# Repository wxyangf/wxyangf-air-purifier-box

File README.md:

Corsi-Rosenthol Inspired Air Purifier

Onshape Available Here: https://cad.onshape.com/documents/9fe4c8aaf9f949d23d7b46f2/w/0d3218e59a3f068a2d390f4a/e/8d3bb73142d813d5a04eb98a (This Is Based on the version tagged "Public Release")

The concept was to have a Corsi-Rosenthol like design, but a bit more refined.

The big problem that I aimed to address with this design is the difficulty of changing the filters in a regular Corsi-Rosenthol air purifier.

no flow rate tests, because it will heavily depend on the fans you decide to use.

TODO:

* write a proper bom
* add assembly instructions
* update the clip design to not self loosen if turned CCW
* add design for decorative side panels

images:

Notes:

I was too lazy to design my own so voltage regulator part used: https://www.amazon.com/dp/B07VVXF7YX

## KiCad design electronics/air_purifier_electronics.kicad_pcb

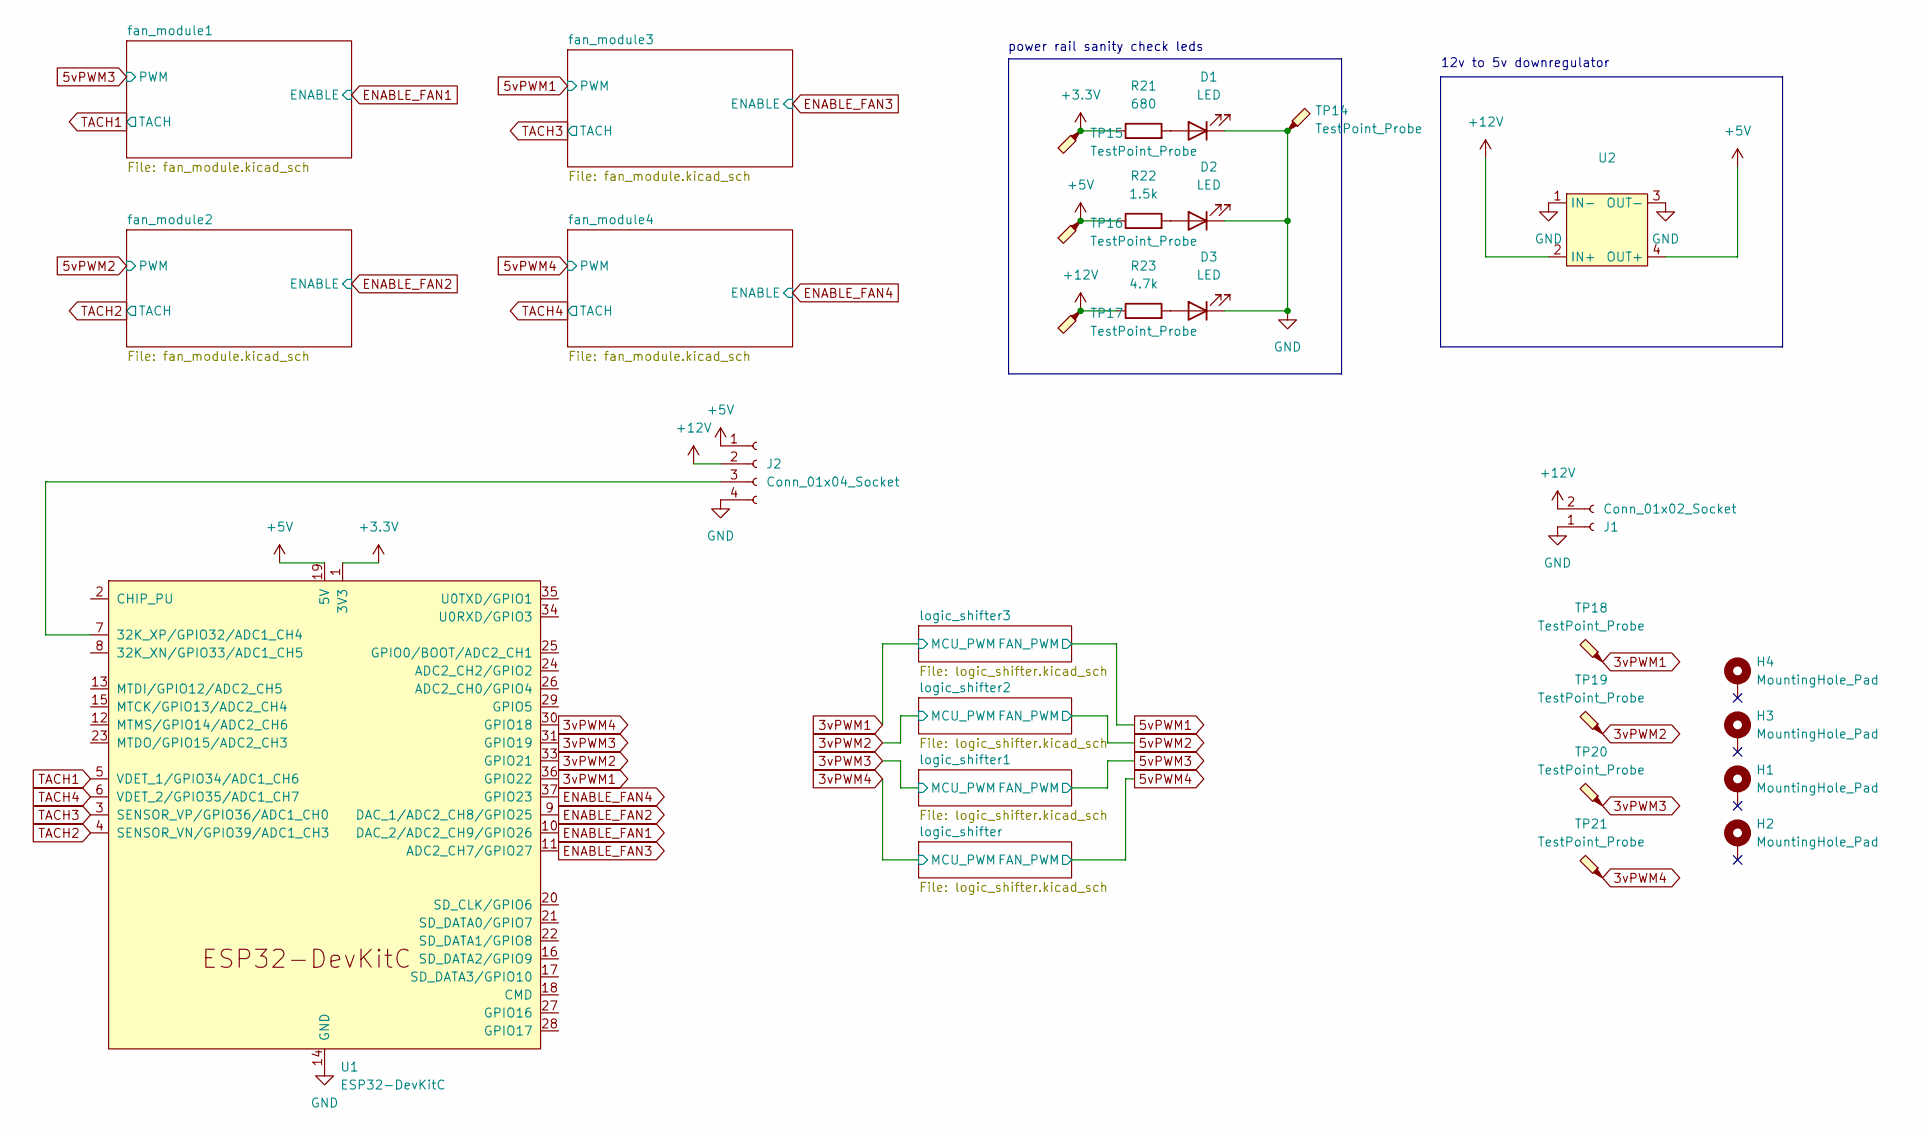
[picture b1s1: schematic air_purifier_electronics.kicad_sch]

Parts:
D1, D2, D3: LED; LED_0805_2012Metric_Pad1.15x1.40mm_HandSolder; LCSC C2296
H1, H2, H3, H4: MountingHole_Pad; MountingHole_3.2mm_M3_DIN965_Pad
J1: Conn_01x02_Socket; AMASS_XT30U-M_1x02_P5.0mm_Vertical
J2: Conn_01x04_Socket; TerminalBlock_Altech_AK300-4_P5.00mm
R21: 680; R_0805_2012Metric_Pad1.20x1.40mm_HandSolder; LCSC C17798
R22: 1.5k; R_0805_2012Metric_Pad1.20x1.40mm_HandSolder; LCSC C4310
R23: 4.7k; R_0805_2012Metric_Pad1.20x1.40mm_HandSolder; LCSC C22356680
TP14, TP15, TP16, TP17, TP18, TP19, TP20, TP21: TestPoint_Probe; TestPoint_THTPad_2.0x2.0mm_Drill1.0mm
U1: ESP32-DevKitC; nodemcu-32s
U2: buck_boost_module

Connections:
3vPWM1: TP18.1, U1.36 (GPIO22); also elsewhere on the board
3vPWM2: TP19.1, U1.33 (GPIO21); also elsewhere on the board
3vPWM3: TP20.1, U1.31 (GPIO19); also elsewhere on the board
3vPWM4: TP21.1, U1.30 (GPIO18); also elsewhere on the board
+3.3V: R21.1, TP15.1, U1.1 (3V3); also elsewhere on the board
+5V: J2.1, R22.1, TP16.1, U1.19 (5V), U2.4 (OUT+)
+12V: J1.2, J2.2, R23.1, TP17.1, U2.2 (IN+); also elsewhere on the board
ENABLE_FAN1: U1.10 (DAC_2/ADC2_CH9/GPIO26); also elsewhere on the board
ENABLE_FAN2: U1.9 (DAC_1/ADC2_CH8/GPIO25); also elsewhere on the board
ENABLE_FAN3: U1.11 (ADC2_CH7/GPIO27); also elsewhere on the board
ENABLE_FAN4: U1.37 (GPIO23); also elsewhere on the board
GND: D1.1 (K), D2.1 (K), D3.1 (K), J1.1, J2.4, TP14.1, U1.14 (GND), U1.32 (GND), U1.38 (GND), U2.1 (IN-), U2.3 (OUT-); also elsewhere on the board
unnamed: D1.2 (A), R21.2
unnamed: D2.2 (A), R22.2
unnamed: D3.2 (A), R23.2
unnamed: J2.3, U1.7 (32K_XP/GPIO32/ADC1_CH4)
TACH1: U1.5 (VDET_1/GPIO34/ADC1_CH6); also elsewhere on the board
TACH2: U1.4 (SENSOR_VN/GPIO39/ADC1_CH3); also elsewhere on the board
TACH3: U1.3 (SENSOR_VP/GPIO36/ADC1_CH0); also elsewhere on the board
TACH4: U1.6 (VDET_2/GPIO35/ADC1_CH7); also elsewhere on the board

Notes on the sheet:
12v to 5v downregulator
power rail sanity check leds

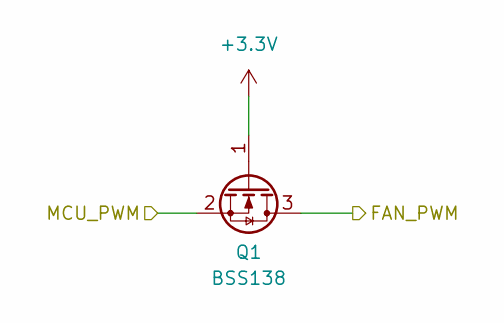
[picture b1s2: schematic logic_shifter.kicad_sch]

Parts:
Q1: BSS138; SOT-23

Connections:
3vPWM4: Q1.2 (S); also elsewhere on the board
5vPWM4: Q1.3 (D); also elsewhere on the board
+3.3V: Q1.1 (G); also elsewhere on the board

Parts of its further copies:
Q2, Q3, Q4: BSS138; SOT-23

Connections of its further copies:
3vPWM1: Q2.2 (S); also elsewhere on the board
3vPWM2: Q3.2 (S); also elsewhere on the board
3vPWM3: Q4.2 (S); also elsewhere on the board
5vPWM1: Q2.3 (D); also elsewhere on the board
5vPWM2: Q3.3 (D); also elsewhere on the board
5vPWM3: Q4.3 (D); also elsewhere on the board
+3.3V: Q2.1 (G), Q3.1 (G), Q4.1 (G); also elsewhere on the board

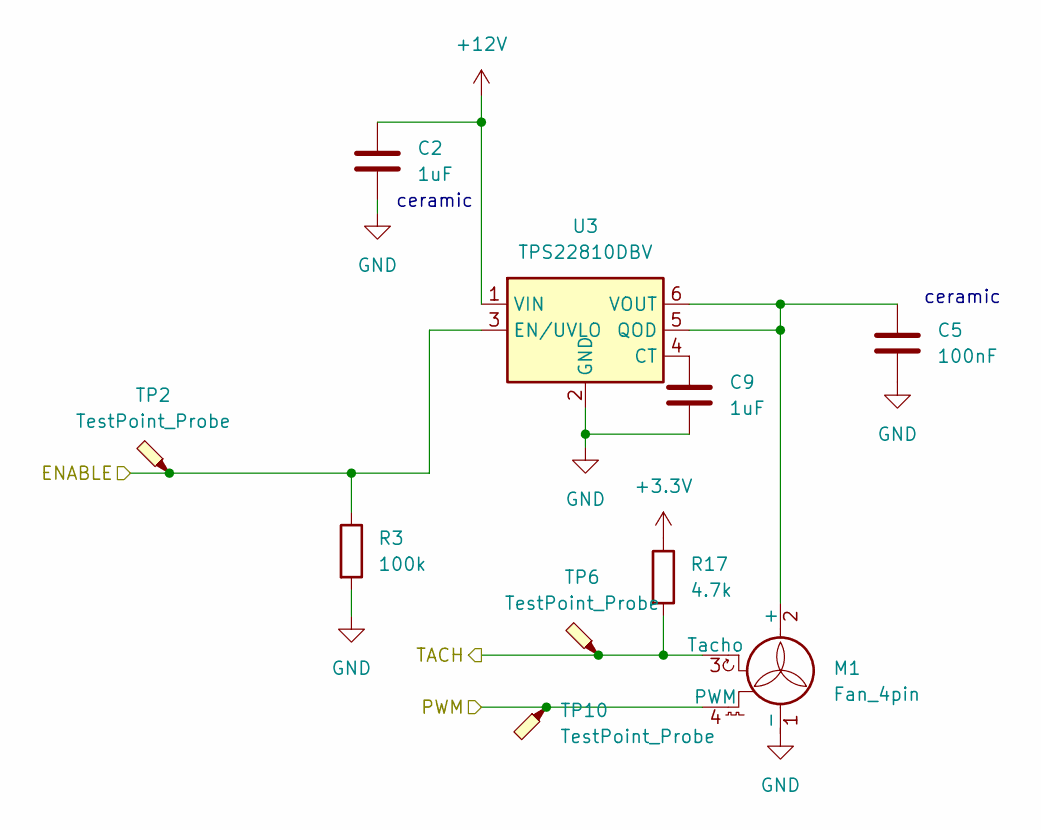
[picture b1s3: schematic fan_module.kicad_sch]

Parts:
C2, C9: 1uF; C_0805_2012Metric_Pad1.18x1.45mm_HandSolder
C5: 100nF; C_0805_2012Metric_Pad1.18x1.45mm_HandSolder
M1: Fan_4pin; FanPinHeader_1x04_P2.54mm_Vertical; LCSC C19795120
R3: 100k; R_0805_2012Metric_Pad1.20x1.40mm_HandSolder; LCSC C22356675
R17: 4.7k; R_0805_2012Metric_Pad1.20x1.40mm_HandSolder; LCSC C22356680
TP2, TP6, TP10: TestPoint_Probe; TestPoint_THTPad_2.0x2.0mm_Drill1.0mm
U3: TPS22810DBV; SOT-23-6

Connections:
5vPWM4: M1.4 (PWM), TP10.1; also elsewhere on the board
+3.3V: R17.1; also elsewhere on the board
+12V: C2.1, U3.1 (VIN); also elsewhere on the board
ENABLE_FAN4: R3.1, TP2.1, U3.3 (EN/UVLO); also elsewhere on the board
GND: C2.2, C5.2, C9.2, M1.1 (-), R3.2, U3.2 (GND); also elsewhere on the board
unnamed: C5.1, M1.2 (+), U3.5 (QOD), U3.6 (VOUT)
unnamed: C9.1, U3.4 (CT)
TACH4: M1.3 (Tacho), R17.2, TP6.1; also elsewhere on the board

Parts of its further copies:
C1, C3, C4, C10, C11, C12: 1uF; C_0805_2012Metric_Pad1.18x1.45mm_HandSolder
C6, C7, C8: 100nF; C_0805_2012Metric_Pad1.18x1.45mm_HandSolder
M2, M3, M4: Fan_4pin; FanPinHeader_1x04_P2.54mm_Vertical; LCSC C19795120
R6, R10, R14: 100k; R_0805_2012Metric_Pad1.20x1.40mm_HandSolder; LCSC C22356675
R18, R19, R20: 4.7k; R_0805_2012Metric_Pad1.20x1.40mm_HandSolder; LCSC C22356680
TP3, TP4, TP5, TP7, TP8, TP9, TP11, TP12, TP13: TestPoint_Probe; TestPoint_THTPad_2.0x2.0mm_Drill1.0mm
U4, U5, U6: TPS22810DBV; SOT-23-6

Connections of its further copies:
5vPWM1: M4.4 (PWM), TP13.1; also elsewhere on the board
5vPWM2: M3.4 (PWM), TP12.1; also elsewhere on the board
5vPWM3: M2.4 (PWM), TP11.1; also elsewhere on the board
+3.3V: R18.1, R19.1, R20.1; also elsewhere on the board
+12V: C1.1, C3.1, C4.1, U4.1 (VIN), U5.1 (VIN), U6.1 (VIN); also elsewhere on the board
ENABLE_FAN1: R6.1, TP3.1, U4.3 (EN/UVLO); also elsewhere on the board
ENABLE_FAN2: R10.1, TP4.1, U5.3 (EN/UVLO); also elsewhere on the board
ENABLE_FAN3: R14.1, TP5.1, U6.3 (EN/UVLO); also elsewhere on the board
GND: C1.2, C3.2, C4.2, C6.2, C7.2, C8.2, C10.2, C11.2, C12.2, M2.1 (-), M3.1 (-), M4.1 (-), R6.2, R10.2, R14.2, U4.2 (GND), U5.2 (GND), U6.2 (GND); also elsewhere on the board
unnamed: C6.1, M2.2 (+), U4.5 (QOD), U4.6 (VOUT)
unnamed: C7.1, M3.2 (+), U5.5 (QOD), U5.6 (VOUT)
unnamed: C8.1, M4.2 (+), U6.5 (QOD), U6.6 (VOUT)
unnamed: C10.1, U4.4 (CT)
unnamed: C11.1, U5.4 (CT)
unnamed: C12.1, U6.4 (CT)
TACH1: M2.3 (Tacho), R18.2, TP7.1; also elsewhere on the board
TACH2: M3.3 (Tacho), R19.2, TP8.1; also elsewhere on the board
TACH3: M4.3 (Tacho), R20.2, TP9.1; also elsewhere on the board

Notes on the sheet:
ceramic

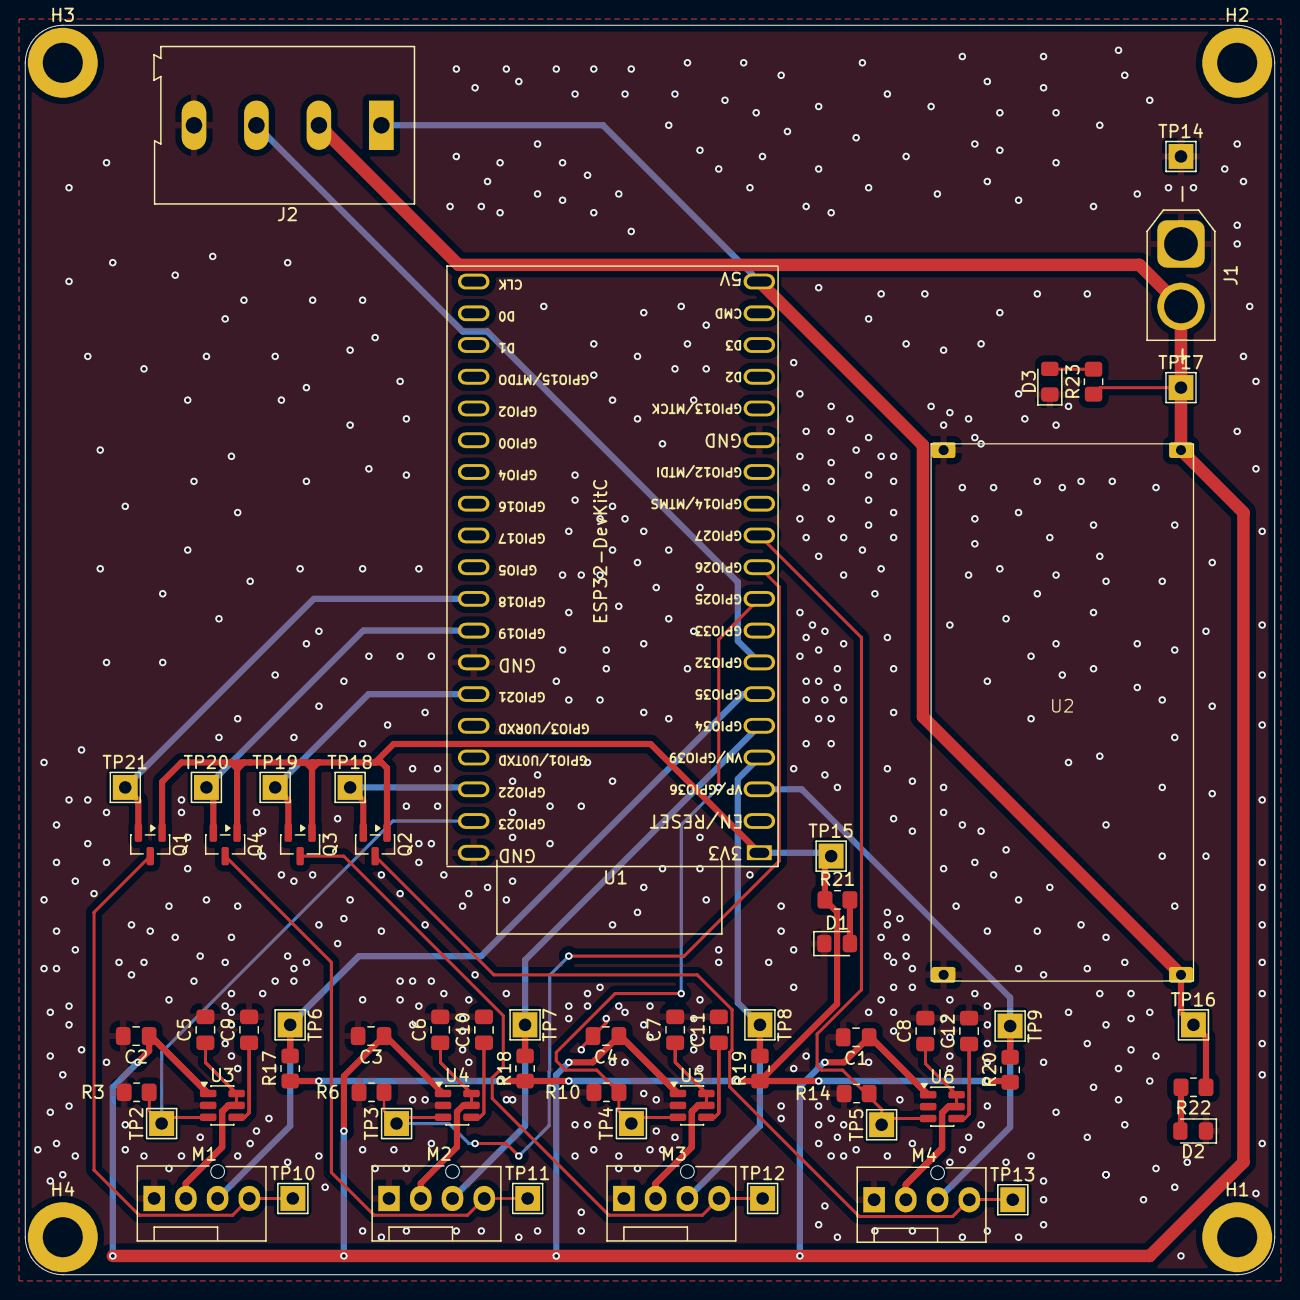
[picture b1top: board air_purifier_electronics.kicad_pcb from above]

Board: 2 copper layers, 100.0 x 100.0 mm, 66 parts (0 on the bottom side), 32 nets.

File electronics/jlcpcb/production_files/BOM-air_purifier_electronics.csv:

Comment,Designator,Footprint,LCSC,Quantity
1.5k,R22,R_0805_2012Metric_Pad1.20x1.40mm_HandSolder,C4310,1
100k,"R10,R14,R3,R6",R_0805_2012Metric_Pad1.20x1.40mm_HandSolder,C22356675,4
4.7k,"R17,R18,R19,R20,R23",R_0805_2012Metric_Pad1.20x1.40mm_HandSolder,C22356680,5
680,R21,R_0805_2012Metric_Pad1.20x1.40mm_HandSolder,C17798,1
BSS138,"Q1,Q2,Q3,Q4",SOT-23,C52895,4
Fan_4pin,"M1,M2,M3,M4",FanPinHeader_1x04_P2.54mm_Vertical,C19795120,4
LED,"D1,D2,D3",LED_0805_2012Metric_Pad1.15x1.40mm_HandSolder,C2296,3
TPS22810DBV,"U3,U4,U5,U6",SOT-23-6,C205990,4
Conn_01x04_Socket,J2,TerminalBlock_Altech_AK300-4_P5.00mm,,1
TestPoint_Probe,TP7,TestPoint_THTPad_2.0x2.0mm_Drill1.0mm,,1
TestPoint_Probe,TP16,TestPoint_THTPad_2.0x2.0mm_Drill1.0mm,,1
Conn_01x02_Socket,J1,AMASS_XT30U-M_1x02_P5.0mm_Vertical,,1
TestPoint_Probe,TP14,TestPoint_THTPad_2.0x2.0mm_Drill1.0mm,,1
TestPoint_Probe,TP18,TestPoint_THTPad_2.0x2.0mm_Drill1.0mm,,1
TestPoint_Probe,TP3,TestPoint_THTPad_2.0x2.0mm_Drill1.0mm,,1
TestPoint_Probe,TP17,TestPoint_THTPad_2.0x2.0mm_Drill1.0mm,,1
TestPoint_Probe,TP9,TestPoint_THTPad_2.0x2.0mm_Drill1.0mm,,1
TestPoint_Probe,TP15,TestPoint_THTPad_2.0x2.0mm_Drill1.0mm,,1
TestPoint_Probe,TP4,TestPoint_THTPad_2.0x2.0mm_Drill1.0mm,,1
TestPoint_Probe,TP10,TestPoint_THTPad_2.0x2.0mm_Drill1.0mm,,1
TestPoint_Probe,TP11,TestPoint_THTPad_2.0x2.0mm_Drill1.0mm,,1
TestPoint_Probe,TP13,TestPoint_THTPad_2.0x2.0mm_Drill1.0mm,,1
1uF,C3,C_0805_2012Metric_Pad1.18x1.45mm_HandSolder,,1
TestPoint_Probe,TP20,TestPoint_THTPad_2.0x2.0mm_Drill1.0mm,,1
1uF,C2,C_0805_2012Metric_Pad1.18x1.45mm_HandSolder,,1
1uF,C4,C_0805_2012Metric_Pad1.18x1.45mm_HandSolder,,1
TestPoint_Probe,TP5,TestPoint_THTPad_2.0x2.0mm_Drill1.0mm,,1
~,U2,buck_boost_module,,1
TestPoint_Probe,TP21,TestPoint_THTPad_2.0x2.0mm_Drill1.0mm,,1
TestPoint_Probe,TP2,TestPoint_THTPad_2.0x2.0mm_Drill1.0mm,,1
TestPoint_Probe,TP8,TestPoint_THTPad_2.0x2.0mm_Drill1.0mm,,1
1uF,C1,C_0805_2012Metric_Pad1.18x1.45mm_HandSolder,,1
TestPoint_Probe,TP19,TestPoint_THTPad_2.0x2.0mm_Drill1.0mm,,1
TestPoint_Probe,TP12,TestPoint_THTPad_2.0x2.0mm_Drill1.0mm,,1
TestPoint_Probe,TP6,TestPoint_THTPad_2.0x2.0mm_Drill1.0mm,,1
ESP32-DevKitC,U1,nodemcu-32s,,1
1uF,C9,C_0805_2012Metric_Pad1.18x1.45mm_HandSolder,,1
100nF,C5,C_0805_2012Metric_Pad1.18x1.45mm_HandSolder,,1
100nF,C6,C_0805_2012Metric_Pad1.18x1.45mm_HandSolder,,1
1uF,C10,C_0805_2012Metric_Pad1.18x1.45mm_HandSolder,,1
100nF,C8,C_0805_2012Metric_Pad1.18x1.45mm_HandSolder,,1
100nF,C7,C_0805_2012Metric_Pad1.18x1.45mm_HandSolder,,1
1uF,C11,C_0805_2012Metric_Pad1.18x1.45mm_HandSolder,,1
1uF,C12,C_0805_2012Metric_Pad1.18x1.45mm_HandSolder,,1

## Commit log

2026-05-29 init commit
